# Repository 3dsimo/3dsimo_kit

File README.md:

# 3Dsimo KIT information

## Watch our PROMO video for 3Dsimo KIT 2 product

Visit us at [3D simo pages](https://3dsimo.com/) for more information

## [3D printed parts](documents/3Dprint.md)
This section includes information about all 3D printed plastic parts. Folder [3Dmodels](3Dmodels) includes all parts in STP and STL formats for both version of 3Dsimo KIT. You can download it and edited it as you want. If your models will be awsome, we can publish them here.

## [Hardware for 3Dsimo KIT](documents/Hardware.md)
Electronics device is an essential part of the 3Dsimo KIT. Main board is a "heart" of the device and manage all functions such as heating, identification or extrusion. 

## [Firmware for 3Dsimo KIT](documents/Firmware.md)
Microcontroller requries a program which can run the device. 3Dsimo KIT has code written in C/C++ language in [Arduino IDE](https://www.arduino.cc/) and it is easy to edit.

## [Arduino nano](documents/ArduinoNano.md)
Information about Arduino Nano like development board. 

## [Manuals](documents/Manual.md)
Manual for device operations and how to edit your Arduino Nano like development kit for 3Dsimo KIT. 

<!--
## [Material profiles](documents/MaterialProfiles.md)
-->

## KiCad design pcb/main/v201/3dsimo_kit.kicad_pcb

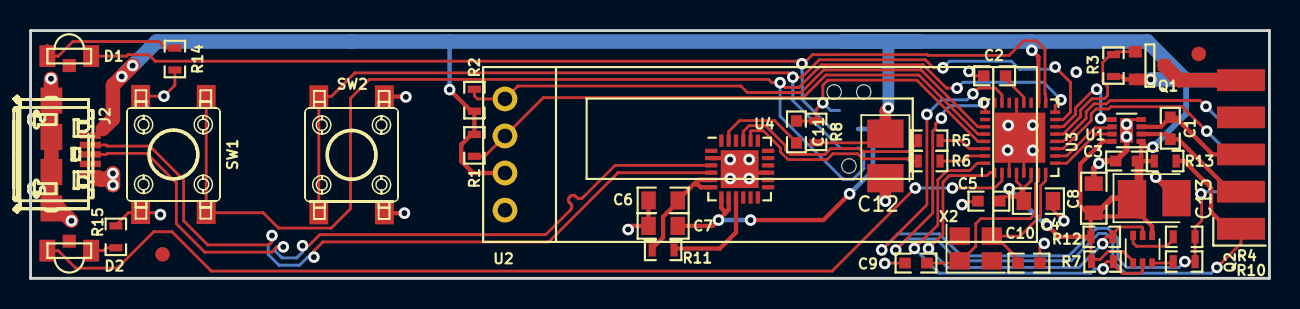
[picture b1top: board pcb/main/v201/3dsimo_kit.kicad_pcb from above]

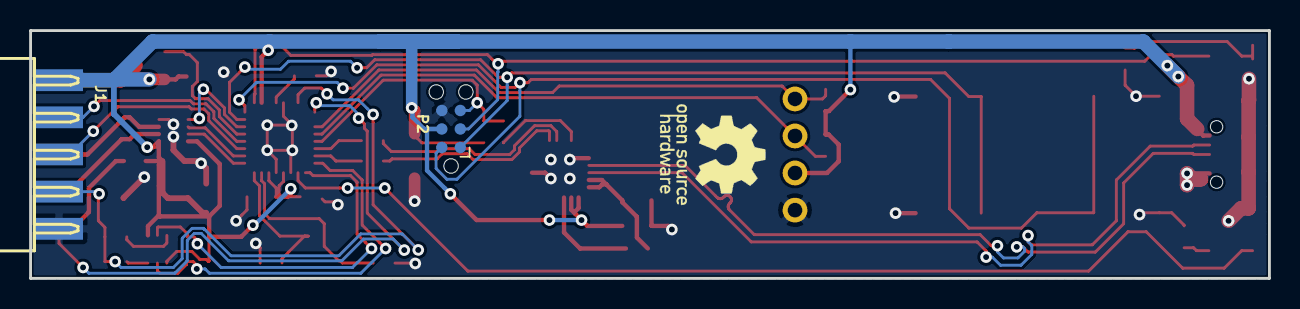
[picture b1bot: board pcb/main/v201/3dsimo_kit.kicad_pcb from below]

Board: 2 copper layers, 85.0 x 17.0 mm, 44 parts (3 on the bottom side), 38 nets.

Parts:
C1, C2, C5, C11: C-100n/50V; C_0603
C3: 1u/25V; C_0603
C4, C6, C7, C8: 22u/10V; C_0805
C9, C10: 12p; C_0603
C12, C13: 100u_6.3V; CP_Tantalum_Case-B_EIA-3528-21_Reflow
D1, D2: KPA-3010CGCK; KPA-3010
J1: CONN_02X05; Header_for_PCB_edge_2x5_2.54mm
J2: MCR-B-S-RA-TSMT-TR
J3, J4: FiducialMark; AssemblyMark_1.0mm
P2: TC2030-ISP; Tag-Connect_TC2030-IDC-NL
Q1: DMG2305UX; SOT-23
Q2: NX3008; SOT-363_SC-70-6
R1, R2, R11, R14, R15: 1k; R_0603
R3, R7, R12, R13: 100k; R_0603
R4, R5, R6: 100R; R_0603
R8, R10: 10k; R_0603
SW1, SW2: TACTM-64N-F
U1: DRV8837; VDFN-8-1EP_2x2mm_Pitch0.5mm
U2: OLED_128x32_MODULE; OLED_MODULE_128x32_IIC
U3: ATMEGA328P-MU; QFN-32-1EP_5x5mm_Pitch0.5mm
U4: CP2102N-QFN24; QFN-24-1EP_4x4mm_Pitch0.5mm
X1: OSHW; OpenHW_6_9x7_3mm
X2: 16MHz; Crystal_SMD_3225-4pin_3.2x2.5mm

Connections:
/BTN_DOWN: P2.2, SW1.2, U3.16
/BTN_EXTRUSION: J1.8, U3.12
/BTN_REVERSE: J1.6, U3.11
/BTN_UP: P2.1, SW2.2, U3.15
/CP_RxD: R6.2, U4.20
/CP_TxD: R5.1, U4.21
/D+: J2.3, U4.3
/D-: J2.2, U4.4
/ID: J1.1, R13.2, U3.25
/MOTOR1: C1.2, J1.3, U1.2
/MOTOR2: C1.1, J1.5, U1.3
/MOTOR_DIR: U1.6, U3.10
/MOTOR_PWM: U1.5, U3.14
/MOTOR_SLEEP: U1.7, U3.9
/NTC: J1.4, R4.2, R10.2, U3.23
/NTC_H_EN: Q2.5, R12.1, U3.1
/NTC_L_EN: Q2.2, R7.2, U3.32
/PWR_OUTPUT: Q1.1, R3.2, U3.13
/RST: C11.1, P2.5, R8.2, U3.29
/SCL: R1.2, U2.2, U3.28
/SDA: R2.2, U2.1, U3.27
GND: C2.2, C3.2, C4.1, C5.2, C6.1, C7.2, C8.1, C9.2, C10.2, C12.2, C13.2, J1.2, J2.5, J2.6, P2.6, R14.2, R15.2, SW1.1, SW2.1, U1.4, U1.9, U2.4, U3.3, U3.5, U3.21, U3.33, U4.2, U4.15, U4.25
unnamed: C2.1, U3.20
unnamed: C9.1, U3.7, X2.1
unnamed: C10.1, U3.8, X2.3
unnamed: C11.2, U4.23
unnamed: D1.1, R14.1
unnamed: D1.2, P2.3, U3.17
unnamed: D2.1, R15.1
unnamed: D2.2, U3.2
unnamed: J1.9, Q1.3
unnamed: Q2.3, R10.1
unnamed: Q2.6, R4.1
unnamed: R5.2, U3.30
unnamed: R6.1, U3.31
unnamed: R11.1, U4.9
VBUS: C3.1, C4.2, C5.1, C7.1, C8.2, C12.1, C13.1, J1.10, J2.1, P2.4, Q1.2, Q2.1, Q2.4, R1.1, R2.1, R3.1, R7.1, R8.1, R12.2, R13.1, U1.1, U1.8, U2.3, U3.4, U3.6, U3.18, U4.7, U4.8
VDD: C6.2, R11.2, U4.5, U4.6

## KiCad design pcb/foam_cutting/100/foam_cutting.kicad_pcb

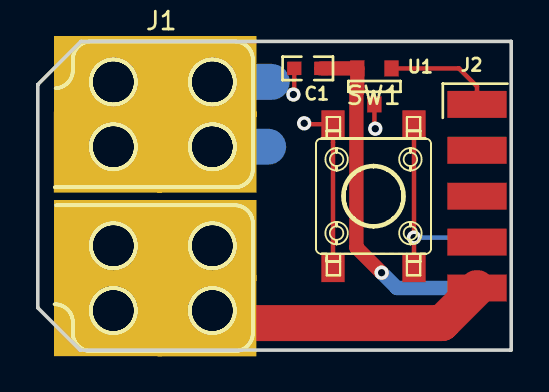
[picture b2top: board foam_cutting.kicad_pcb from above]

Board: 2 copper layers, 26.3 x 17.1 mm, 5 parts (0 on the bottom side), 5 nets.

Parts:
C1: C-100n_50V; C_0603
J1: FoamCutting; FoamCutting_110x80mm
J2: CONN_02X05; Header_for_PCB_edge_male_2x5_2.54mm
SW1: DTSM-61K-V-B; SW_SPST_6x6mm_H4.3mm
U1: 11AA01_TT; SOT-23

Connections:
GND: C1.2, J1.1, J2.2, SW1.2, U1.3
unnamed: J1.2, J2.9
unnamed: J2.1, U1.1
unnamed: J2.8, SW1.1
VCC: C1.1, J2.10, U1.2

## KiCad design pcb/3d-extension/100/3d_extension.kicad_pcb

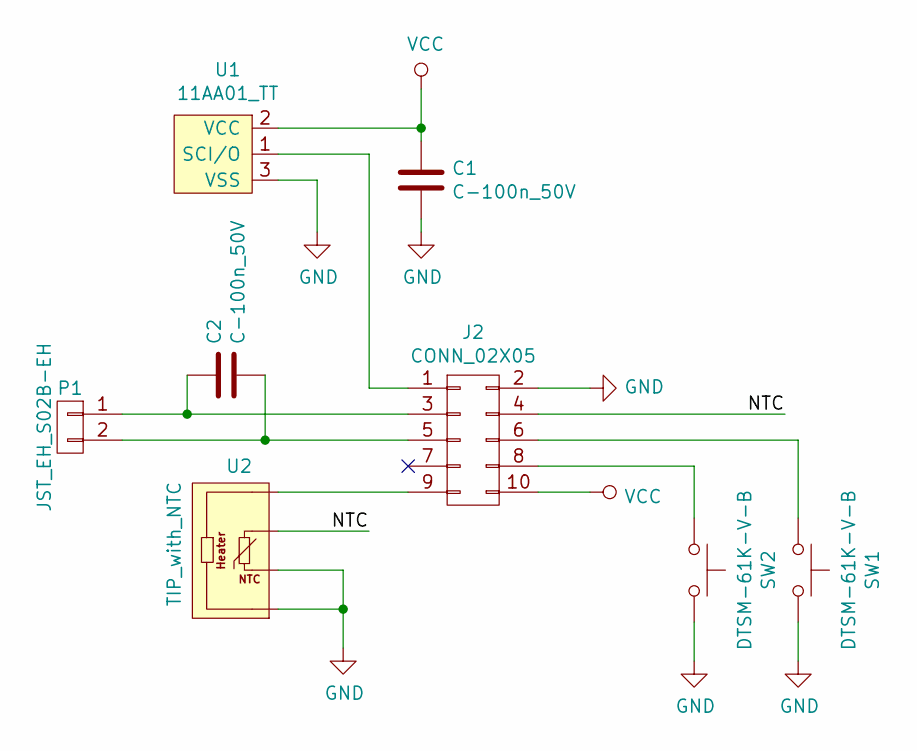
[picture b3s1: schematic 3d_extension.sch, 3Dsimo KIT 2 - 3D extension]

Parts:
C1, C2: C-100n_50V; C_0603
J2: CONN_02X05; Header_for_PCB_edge_male_2x5_2.54mm
P1: JST_EH_S02B-EH; JST_EH_S02B-EH_02x2.50mm_Angled
SW1, SW2: DTSM-61K-V-B; SW_SPST_6x6mm_H4.3mm
U1: 11AA01_TT; SOT-23
U2: TIP_with_NTC; HOLDER_TIP_NTC_CN

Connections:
/NTC: J2.4, U2.3 (NTC)
GND: C1.2, J2.2, SW1.2, SW2.2, U1.3 (VSS), U2.1 (PWR), U2.2 (NTC)
unnamed: C2.1, J2.3, P1.1
unnamed: C2.2, J2.5, P1.2
unnamed: J2.1, U1.1 (SCI/O)
unnamed: J2.6, SW1.1
unnamed: J2.8, SW2.1
unnamed: J2.9, U2.4 (PWR)
VCC: C1.1, J2.10, U1.2 (VCC)

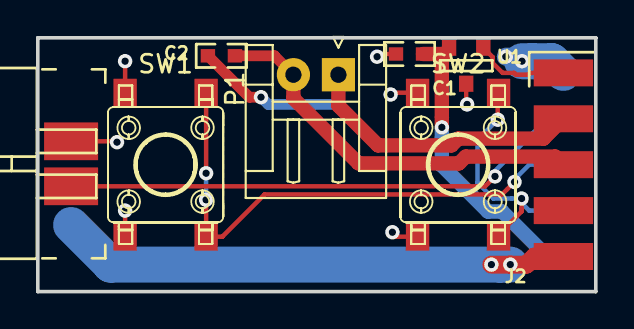
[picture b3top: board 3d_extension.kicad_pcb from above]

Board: 2 copper layers, 31.0 x 14.1 mm, 8 parts (1 on the bottom side), 9 nets.

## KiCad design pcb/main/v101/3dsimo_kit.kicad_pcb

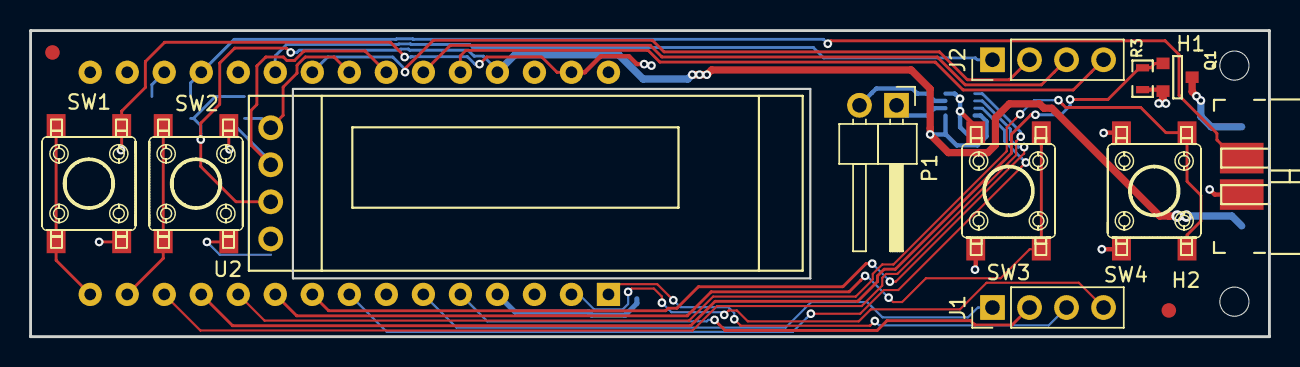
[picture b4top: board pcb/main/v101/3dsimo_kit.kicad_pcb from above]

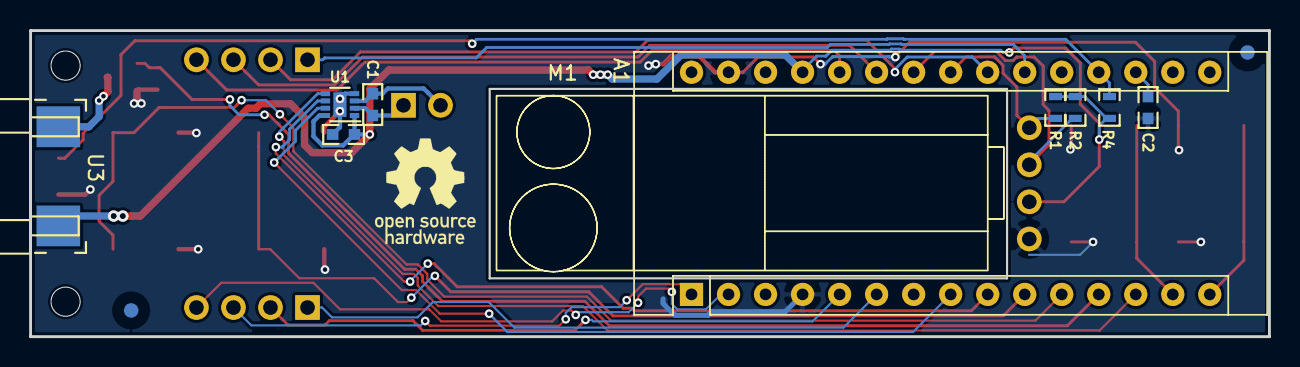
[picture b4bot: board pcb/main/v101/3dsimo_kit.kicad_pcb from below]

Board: 2 copper layers, 85.0 x 21.0 mm, 27 parts (13 on the bottom side), 25 nets.

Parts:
A1: Arduino_Nano_v3.x; Arduino_Nano
C1, C2: C-100n/50V; C_0603
C3: 1u/6.3V; C_0603
H1, H2: HOLE; MountingHole_2.0mm
J1, J2: CONN_01X04; Pin_Header_Straight_1x04_Pitch2.54mm
J3, J4, J5, J6: FiducialMark; AssemblyMark_1.0mm
M1: Motor; MotorWithTransmission
P1: PinHeader 2.54mm; Pin_Header_Angled_1x02_Pitch2.54mm
Q1: IRLML0030; SOT-23
R1, R2: 4.7k; R_0603
R3: 100k; R_0603
R4: 100R; R_0603
SW1, SW2, SW3, SW4: TACTM-64N-F
U1: DRV8837; VDFN-8-1EP_2x2mm_Pitch0.5mm
U2: OLED_128x32_MODULE; OLED_MODULE_128x32_IIC
U3: TIP_with_NTC; HOLDER_TIP_NTC_CN
X1: OSHW; OpenHW_6_9x7_3mm

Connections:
/BTN_DOWN: A1.15, SW1.2
/BTN_EXTRUSION: A1.11, SW4.2
/BTN_REVERSE: A1.10, SW3.2
/BTN_UP: A1.14, SW2.2
/MOTOR_DIR: A1.9, U1.6
/MOTOR_PWM: A1.13, U1.5
/MOTOR_SLEEP: A1.8, U1.7
/NTC: A1.19, R4.2, U3.3
/PWR_OUTPUT: A1.12, Q1.1, R3.1
GND: A1.4, A1.29, C2.1, C3.2, Q1.2, R3.2, SW1.1, SW2.1, SW3.1, SW4.1, U1.4, U1.9, U2.4, U3.2
unnamed: A1.1, J1.3
unnamed: A1.2, J1.4
unnamed: A1.5, J1.2
unnamed: A1.6, J1.1
unnamed: A1.18, C2.2
unnamed: A1.21, J2.1
unnamed: A1.22, J2.2
unnamed: A1.23, R1.2, U2.1
unnamed: A1.24, R2.2, U2.2
unnamed: A1.25, J2.3
unnamed: A1.26, J2.4
unnamed: C1.1, P1.2, U1.3
unnamed: C1.2, P1.1, U1.2
unnamed: Q1.3, U3.4
VCC: A1.27, C3.1, R1.1, R2.1, R4.1, U1.1, U1.8, U2.3, U3.1

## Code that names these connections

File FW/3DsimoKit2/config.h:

#ifndef _CONFIG_H
#define _CONFIG_H

/*
 *   define Input/Outputs
 */

#define LED_L         13    // LED placed on Arduino Nano board
#define LED_R         4     // LED placed on 3Dsimo KIT opposite to LED_NANO

#define BTN_UP        12    // controlling button UP/PLUS                /* NEW! changed for right hand - default 11 */
#define BTN_DOWN      11    // controlling button DOWN/MINUS             /* NEW! changed for right hand - default 12 */
#define BTN_EXT       7     // button for material extrusion
#define BTN_REV       8     // button for material reverse

#define MOTOR_DIR     6     // motor direction output
#define MOTOR_PWM     10    // motor PWM output for power driving
#define MOTOR_SLEEP   5
#define HEATER_EN     9     // heater/power output 

#define TEMP_IN       A0    // temperature measure ADC input 

#define LOW_TEMP_EN   3     // enable measurement for low temperatures (~from 40deg. Celsius)
#define HIGH_TEMP_EN  2     // enable measurement for high temperatures (~from 150deg. Celsius)

#define ID_PIN        16    // Pin for identification of the accessories

/*
 *   define heating states
 */
enum {
  STATE_HEATING,
  STATE_COOLING,
  STATE_READY,
} STATE_e;

enum {
  MOTOR_STOP,
  MOTOR_EXTRUSION,
  MOTOR_REVERSE,
  MOTOR_CONTINUOUS,
  MOTOR_REVERSE_AFTER_EXTRUSION
} MOTOR_STATE_e;

/*
 *   define structure for the material list
 */
typedef struct {
  int temperature;
  int motorSpeed;
  char* materialName;
} profile_t;

#endif

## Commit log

2018-06-22 added 3D models of housing
2018-06-22 added manuals EN, CZ
2018-07-01 Repaired new STLs and oriented them correctly for 3D print
2018-07-01 Repaired file
2018-07-20 added HW & FW manual
2018-08-06 Add files via upload
    changed orientation of display to suit right-handed people
2018-08-06 Display orientation for right-handed people
    Changed orientation of display to better suit right-handed people
2018-08-21 Firmware Information added
    Brief overview of "What's in this folder?". And some information that should help those who are new to Arduino.
2018-08-21 Added 3D models folder link
2018-08-21 Added links and tips
2018-08-21 Made the links relative...
2018-08-22 Button up-down: if-checks corrected
    The pins are right, but the if-checks in lines 353 and 372 had the "!" confused. Or maybe I'm confused.
2018-08-23 Suggestion: put _JC3D file in it's own subfolder.
    Arduino IDE does not like them in one folder (e.g. if one clones the whole repo). That also explaines the "3DsimoKit" subfolder in FW. This is the one the IDE created... The structure would be less p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
    - FW/3DsimoKit/3DsimoKit.ino
    - FW/3DsimoKit_JC3D/3DsimoKit_JC3D.ino
    - FW/3DsimoKit_anotherNewFW/3DsimoKit_anotherNewFW.ino .... and so on...
    I wrote a quick tip to the README for anyone else getting an error after downloading the whole repo and trying to use one of the files.
2018-08-23 quickfix: juicy typo
    Stopped those assing functions from assing around. :-D
2018-08-24 (init) Implemented UP/DOWN as on-Release-buttons
    This also works a lot better with my pen for some reason. But then again, I should maybe avoid to short-out all those pins on the back side with my hand (oddly, this was never an issue with the ExtRe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
2018-08-25 Working: Change Temperature in 5°C steps with Up & Down buttons
    no code cleanup yet. But it seems to work. New:
    - MINTEMP, MAXTEMP
    - setMotorSpeed hardcoded to 40% TODO
    - displayControls() function to display setMotorSpeed and setTemperature and not display Material Profile names. TODO make it look nicer
    - TODO remove the old unused code, let Up&&Down change the Control Mode between Temperature and Motor, let Up||Down change setMotorSpeed
2018-08-26 Display Layout pretty
    - shuffled text on the display around to prepare it for ControlMode change
    - selected ControlMode will be inverted
    - pretty details: small units, nice alignment, more status text, change symbol in the middle
    - also: corrected the name of the ssd1306 author from Dinda to Dynda (so you can find the correct github when googling his name)
2018-08-26 some cleanup, material profiles removed
2018-08-26 Button Patch: true/false corrected
    LOW=pressed!
    - changed pins 11 & 12 back for right hand
    - the if checks for UP & DOWN changed back to "!"
    - some WIP for two-button-press
    - typo "assing" fix
2018-08-26 typos in the comments
    - Stopped those assing functions from assing around. :-D
    - corrected name of ssd1306 author to Dynda
2018-08-26 initial draft, not proof read yet.
    Especially meant for beginners who never used any 3D pen before. Just what came to my mind. It's late...
2018-08-26 some proof reading and editing
2018-08-27 states for all 4 buttons and as binary bits
    - Because I can't hex
    - BUG: for some reason the Nano reboots when I hit EXT. Only happens with motor... But did not happen yesterday o_O
2018-08-27 Bugged: buttonPressed, WIP
    - need to go, will fix later
    - Reworked the whole UP-DOWN condition tree.
    - the if seems to work (testable with LED), but the buttonPressed flags are not
    - idea: Print the damn 8 bits to the display for debugging
    - when finished: uncomment the LED in ln 271
    - WIP: EXT and REV are commented out, need to finish next
2018-08-27 Awesome Press and Release events for UP, DOWN, BOTH
    - looks good so far!
    - new flag bit for the BOTH state. Lesser errors...
    - for some reason it did not work to only check the bitflag, I had to no-press-check the other button (ln 403, 390)
2018-08-27 ControlMode change functioning. SetMotorSpeed controlable
2018-08-27 EXP and REV back functional. Everything works so far!
    - removed double flag from both button press. No more reboot bugs at EXT.
2018-08-27 Readme with usage guide
2018-08-28 added WIP and bugs info
2018-08-28 OFF mode for temperatures under 153°C
    - New State "OFF" that prevents extrusion
    - Temperature setting will step from 0 directly to 155 and vice versa
    - Display updated to show the status
2018-08-28 Off mode guide. Some fixes.
2018-08-28 just linked the firmware update guide.
2018-08-28 typo
2018-08-29 added some warnings, fixed some typos.
2018-08-29 forgot to push... Cleanup, left-hand notes, max temperature
2018-08-29 Left-hand information
2018-08-29 those typos...
2018-08-29 Releasing UP&DOWN buttons after mode change will not fire a single button action any more
2018-08-29 Removed WIP: everything done!
2018-08-29 Some links to the shop. Some more tipps
2018-09-04 maximum Motorspeed limit to 60%. Safety first.
    To prevent overflow of the nozzle. You should stick to a motor speed around 40 +- 10. If you really need a higher speed: change MAXSPEED in line 59.
2018-09-04 Added info about maximum MotorSpeed
2018-09-04 Corrected line number, added a clear link to the ino file
2018-12-21 added 3d models (STL, STP)
2019-01-02 * Merge righthanded-lefthanded code * button handling simplified (no bit operations) * up/down press: switch handedness * profiles with different speeds * default: PLA 210 degrees
2019-01-02 add info on the sections
2019-01-02 Add images for docs
2019-01-02 extend info on the Nano
2019-01-02 give info on uploading the code
2019-01-02 add photo of display
2019-01-02 Add info on operation
2019-01-02 file from PR AnTi-ArT
    part of PR #3 AnTi-ArT
2019-01-02 part of PR #3 AnTi-ArT
    part of PR #3 AnTi-ArT
2019-01-02 fix arduino link
2019-01-02 Ingegno Enclosure changes
2019-01-02 add respins
2019-01-02 fix link
2019-01-30 Add Dutch Manual for the 3D pen
2019-04-09 fix bug in part 1, better fitting now
2019-10-15 updated v101, added pcb and FW for KIT 2
2019-10-15 moved 3d wrml models
2019-10-15 updated documentation
2019-10-15 edited youtube video
2019-10-15 updated picture with video
2019-11-29 added stp model and manual
2019-12-10 LEDs turn off when cooling
2020-02-21 added screen flip, improved PID controller
2020-03-10 updated profiles
2020-03-10 updated 3D parts
2020-03-11 updated profiles and minor bugfixes
2020-03-12 updated parts locations in sch
2020-04-21 Add files via upload
    Added newer 3D models for KIT2
2020-08-04 Change name of Single button ring
2020-09-29 Add files via upload
    Battery_adaptor_stl_files_added
2020-10-05 version 3 added
2021-11-09 Update Hardware.md
    https://forum.kicad.info/t/warning-avoid-all-links-to-kicad-pcb-org-use-kicad-org/31521
2022-01-28 3DsimoKit2_Freemode
    Updated Kit2 firmware to enable Freemode for the 3D drawing accessory. I updated the Kit2 with changes made to the original Kit by user AnTi-ArT.
2022-01-29 Update accessories_Freemode.c
    Removed sections related to materials profile that is not used with freemode.
